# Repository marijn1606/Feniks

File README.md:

# Feniks

Relatively cheap wifi enabled 4 channel BBQ thermometer based on a ESP32-C3.

The system is powered by an 18650 li-ion battery, and has integrated battery charge and protection circuitry.

The temperature probe data is displayed on a small I2C OLED screen as well as a webserver hosted on the ESP.

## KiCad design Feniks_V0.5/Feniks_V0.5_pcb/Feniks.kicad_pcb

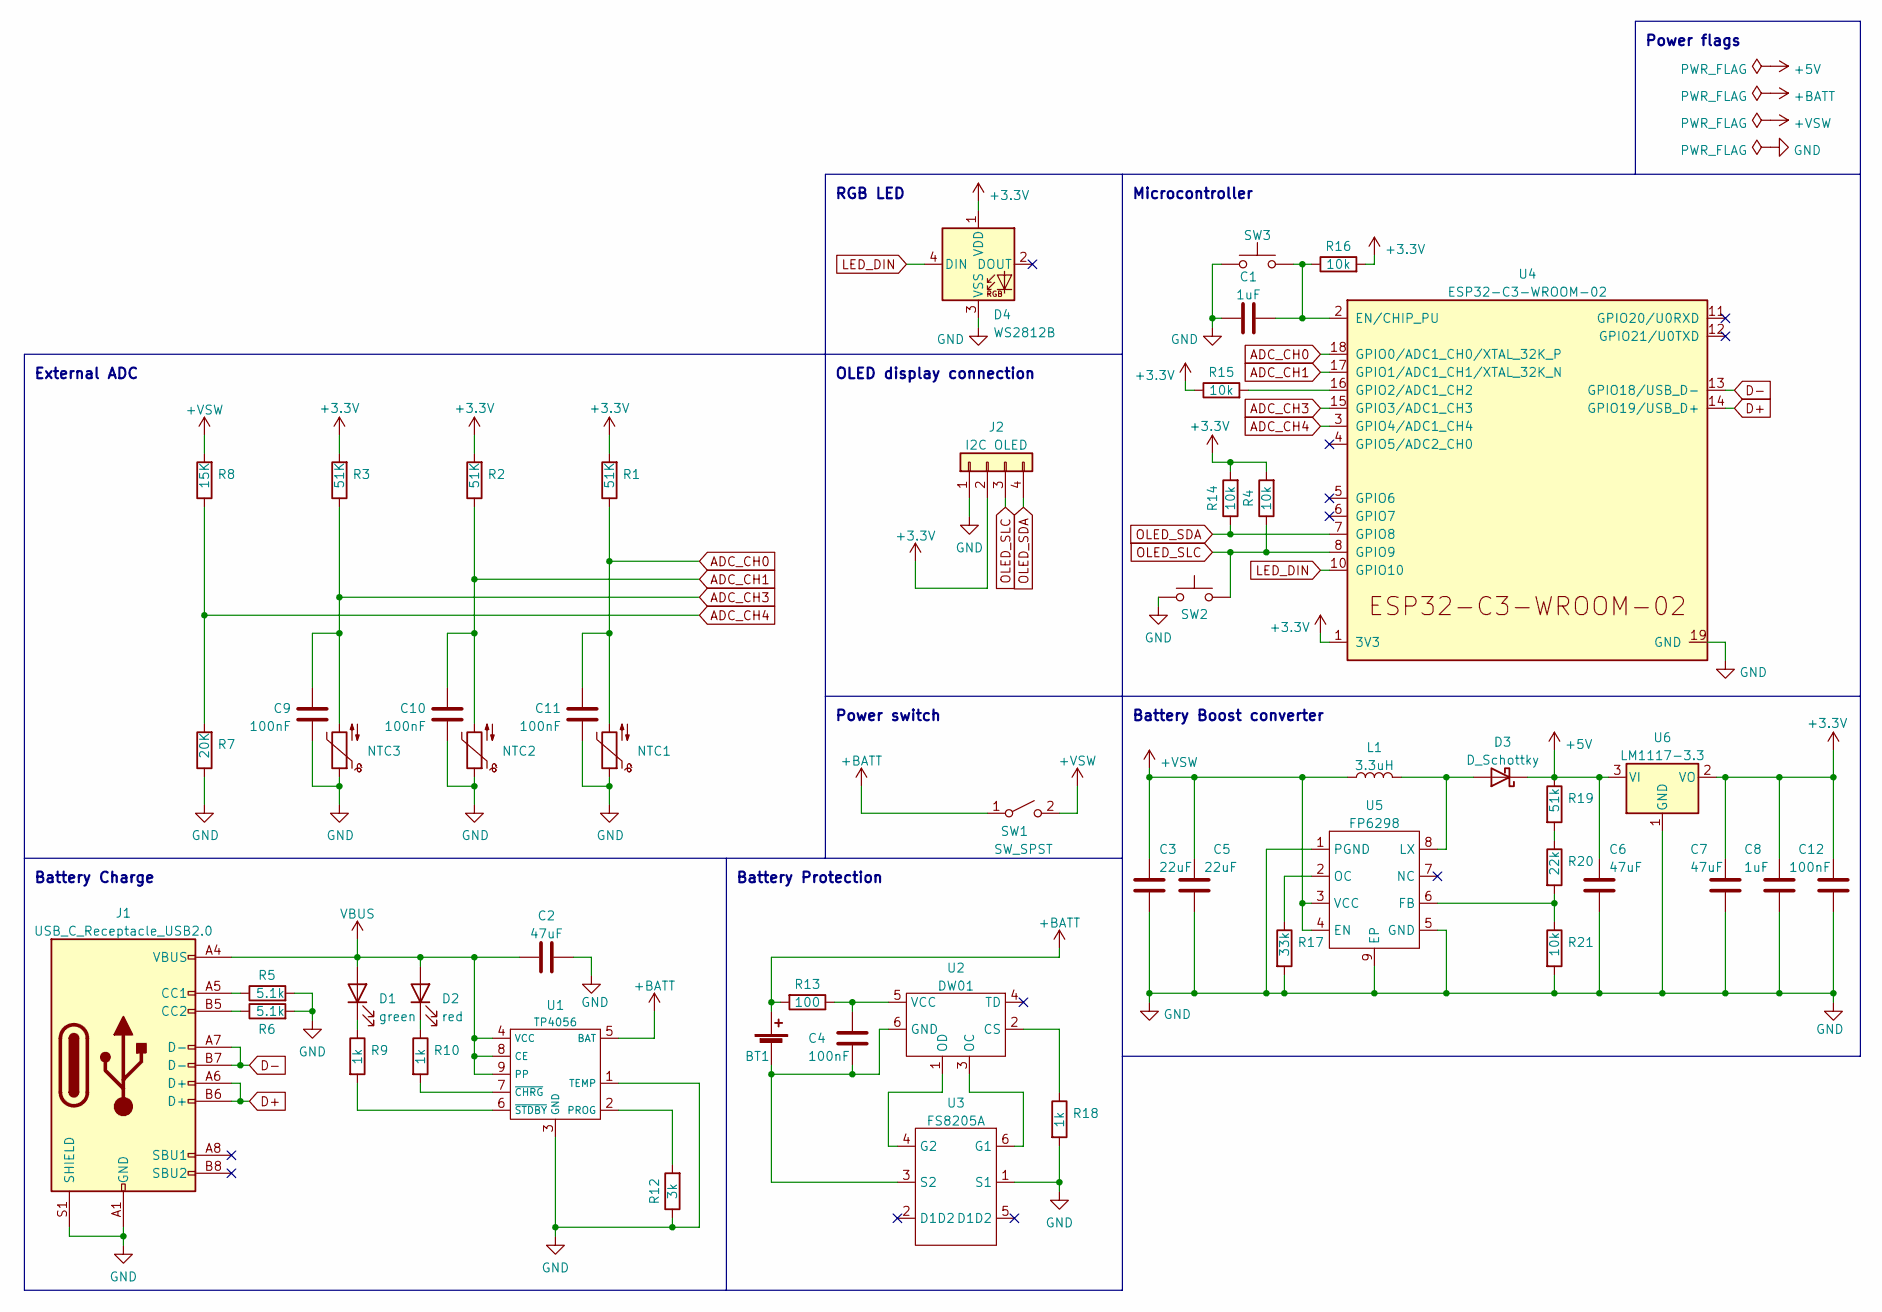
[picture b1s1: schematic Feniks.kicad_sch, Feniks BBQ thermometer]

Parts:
BT1: Battery_Cell; 18650SMT holder
C1, C8: 1uF; C_0805_2012Metric_Pad1.18x1.45mm_HandSolder
C2, C6, C7: 47uF; C_0805_2012Metric_Pad1.18x1.45mm_HandSolder
C3, C5: 22uF; C_0805_2012Metric_Pad1.18x1.45mm_HandSolder
C4, C9, C10, C11, C12: 100nF; C_0805_2012Metric_Pad1.18x1.45mm_HandSolder
D1: green; LED_0805_2012Metric_Pad1.15x1.40mm_HandSolder
D2: red; LED_0805_2012Metric_Pad1.15x1.40mm_HandSolder
D3: D_Schottky; D_SMA
D4: WS2812B; LED_WS2812B_PLCC4_5.0x5.0mm_P3.2mm
J1: USB_C_Receptacle_USB2.0; USB_C_Receptacle_HRO_TYPE-C-31-M-12
J2: I2C OLED; PinSocket_1x04_P2.54mm_Vertical
L1: 3.3uH; CD43
NTC1, NTC2, NTC3: Thermistor_NTC; PinSocket_1x02_P2.54mm_Vertical
R1, R2, R3: 51K; R_0805_2012Metric_Pad1.20x1.40mm_HandSolder
R4, R14, R15, R16, R21: 10k; R_0805_2012Metric_Pad1.20x1.40mm_HandSolder
R5, R6: 5.1k; R_0805_2012Metric_Pad1.20x1.40mm_HandSolder
R7: 20K; R_0805_2012Metric_Pad1.20x1.40mm_HandSolder
R8: 15K; R_0805_2012Metric_Pad1.20x1.40mm_HandSolder
R9, R10, R18: 1k; R_0805_2012Metric_Pad1.20x1.40mm_HandSolder
R12: 3k; R_0805_2012Metric_Pad1.20x1.40mm_HandSolder
R13: 100; R_0805_2012Metric_Pad1.20x1.40mm_HandSolder
R17: 33k; R_0805_2012Metric_Pad1.20x1.40mm_HandSolder
R19: 51k; R_0805_2012Metric_Pad1.20x1.40mm_HandSolder
R20: 22k; R_0805_2012Metric_Pad1.20x1.40mm_HandSolder
SW1: SW_SPST; PinHeader_1x02_P2.54mm_Vertical
SW2, SW3: SW_Push; SW_SPST_CK_RS282G05A3
U1: TP4056; SOIC-8-1EP_3.9x4.9mm_P1.27mm_EP2.29x3mm_ThermalVias
U2: DW01; SOT-23-6_Handsoldering
U3: FS8205A; SOT-23-6_Handsoldering
U4: ESP32-C3-WROOM-02
U5: FP6298; SOIC-8-1EP_3.9x4.9mm_P1.27mm_EP2.29x3mm_ThermalVias
U6: LM1117-3.3; SOT-223-3_TabPin2

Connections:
+3.3V: C7.1, C8.1, C12.1, D4.1 (VDD), J2.2, R1.2, R2.2, R3.2, R4.2, R14.2, R15.1, R16.2, U4.1 (3V3), U6.2 (VO)
+5V: C6.1, D3.1 (K), R19.1, U6.3 (VI)
+BATT: BT1.1 (+), R13.2, SW1.1 (A), U1.5 (BAT)
+VSW: C3.1, C5.1, L1.1, R8.2, SW1.2 (B), U5.3 (VCC), U5.4 (EN)
ADC_CH0: C11.2, NTC1.2, R1.1, U4.18 (GPIO0/ADC1_CH0/XTAL_32K_P)
ADC_CH1: C10.2, NTC2.2, R2.1, U4.17 (GPIO1/ADC1_CH1/XTAL_32K_N)
ADC_CH3: C9.2, NTC3.2, R3.1, U4.15 (GPIO3/ADC1_CH3)
ADC_CH4: R7.2, R8.1, U4.3 (GPIO4/ADC1_CH4)
D+: J1.A6 (D+), J1.B6 (D+), U4.14 (GPIO19/USB_D+)
D-: J1.A7 (D-), J1.B7 (D-), U4.13 (GPIO18/USB_D-)
GND: C1.1, C2.2, C3.2, C5.2, C6.2, C7.2, C8.2, C9.1, C10.1, C11.1, C12.2, D4.3 (VSS), J1.A1 (GND), J1.A12 (GND), J1.B1 (GND), J1.B12 (GND), J1.S1 (SHIELD), J2.1, NTC1.1, NTC2.1, NTC3.1, R5.2, R6.2, R7.1, R12.1, R17.2, R18.2, R21.2, SW2.1, SW3.1, U1.1 (TEMP), U1.3 (GND), U3.1 (S1), U4.9 (GND), U4.19 (GND), U5.1 (PGND), U5.5 (GND), U5.9 (EP), U6.1 (GND)
LED_DIN: D4.4 (DIN), U4.10 (GPIO10)
unnamed: BT1.2 (-), C4.1, U2.6 (GND), U3.3 (S2)
unnamed: C1.2, R16.1, SW3.2, U4.2 (EN/CHIP_PU)
unnamed: C4.2, R13.1, U2.5 (VCC)
unnamed: D1.1 (K), R9.1
unnamed: D2.1 (K), R10.1
unnamed: D3.2 (A), L1.2, U5.8 (LX)
unnamed: J1.A5 (CC1), R5.1
unnamed: J1.B5 (CC2), R6.1
unnamed: R9.2, U1.6 (~STDBY)
unnamed: R10.2, U1.7 (~CHRG)
unnamed: R12.2, U1.2 (PROG)
unnamed: R15.2, U4.16 (GPIO2/ADC1_CH2)
unnamed: R17.1, U5.2 (OC)
unnamed: R18.1, U2.2 (CS)
unnamed: R19.2, R20.1
unnamed: R20.2, R21.1, U5.6 (FB)
unnamed: U2.1 (OD), U3.4 (G2)
unnamed: U2.3 (OC), U3.6 (G1)
OLED_SDA: J2.4, R14.1, U4.7 (GPIO8)
OLED_SLC: J2.3, R4.1, SW2.2, U4.8 (GPIO9)
VBUS: C2.1, D1.2 (A), D2.2 (A), J1.A4 (VBUS), J1.A9 (VBUS), J1.B4 (VBUS), J1.B9 (VBUS), U1.4 (VCC), U1.8 (CE), U1.9 (PP)

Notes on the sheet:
Microcontroller
Power flags
Battery Protection
Battery Boost converter
OLED display connection
RGB LED
Battery Charge
External ADC
Power switch

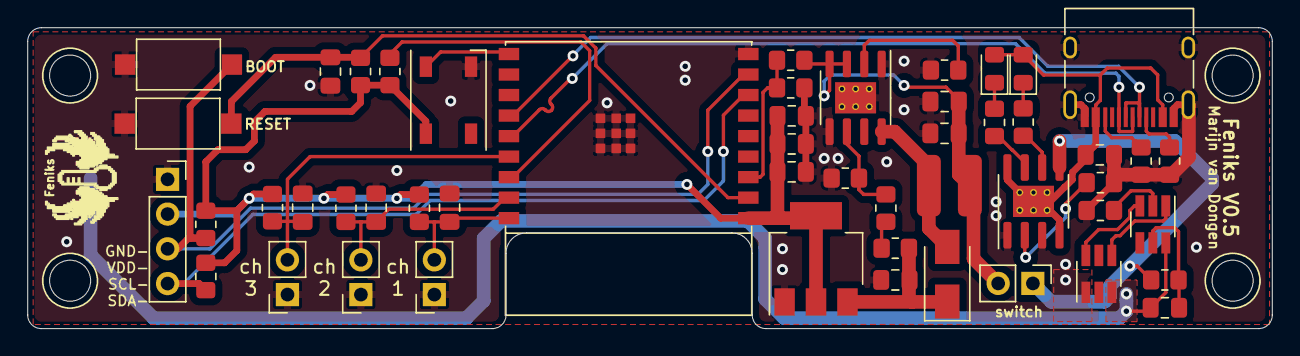
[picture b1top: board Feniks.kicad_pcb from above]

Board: 2 copper layers, 91.0 x 22.0 mm, 52 parts (1 on the bottom side), 33 nets.

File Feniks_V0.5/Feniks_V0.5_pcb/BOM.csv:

"Id;""Designator"";""Package"";""Quantity"";""Designation"";""Supplier and ref"";",,,,,
"1;""C3",C5,C7,C6,C2,"C8"";""C_0805_2012Metric_Pad1.18x1.45mm_HandSolder"";6;""47uF"";;;"
"2;""R10",R18,"R9"";""R_0805_2012Metric_Pad1.20x1.40mm_HandSolder"";3;""1k"";;;",,,
"3;""C11",C12,C4,C10,"C9"";""C_0805_2012Metric_Pad1.18x1.45mm_HandSolder"";5;""100nF"";;;",
"4;""D3"";""D_SMA"";1;""D_Schottky"";;;",,,,,
"5;""R20"";""R_0805_2012Metric_Pad1.20x1.40mm_HandSolder"";1;""68k"";;;",,,,,
"6;""U2"";""SOT-23-6_Handsoldering"";1;""DW01"";;;",,,,,
"7;""U5"";""SOIC-8-1EP_3.9x4.9mm_P1.27mm_EP2.29x3mm_ThermalVias"";1;""FP6298"";;;",,,,,
"8;""D2"";""LED_0805_2012Metric_Pad1.15x1.40mm_HandSolder"";1;""red"";;;",,,,,
"9;""J2"";""PinSocket_1x04_P2.54mm_Vertical"";1;""I2C OLED"";;;",,,,,
"10;""R1",R3,"R2"";""R_0805_2012Metric_Pad1.20x1.40mm_HandSolder"";3;""51K"";;;",,,
"11;""R4",R21,R15,R14,"R16"";""R_0805_2012Metric_Pad1.20x1.40mm_HandSolder"";5;""10k"";;;",
"12;""U4"";""ESP32-C3-WROOM-02"";1;""ESP32-C3-WROOM-02"";;;",,,,,
"13;""L1"";""CD43"";1;""3.3uH"";;;",,,,,
"14;""R5",R6,"R19"";""R_0805_2012Metric_Pad1.20x1.40mm_HandSolder"";3;""5.1k"";;;",,,
"15;""NTC3",NTC2,"NTC1"";""PinSocket_1x02_P2.54mm_Vertical"";3;""Thermistor_NTC"";;;",,,
"16;""C1"";""C_0805_2012Metric_Pad1.18x1.45mm_HandSolder"";1;""1uF"";;;",,,,,
"17;""SW3","SW2"";""SW_SPST_CK_RS282G05A3"";2;""SW_Push"";;;",,,,
"18;""U1"";""SOIC-8-1EP_3.9x4.9mm_P1.27mm_EP2.29x3mm_ThermalVias"";1;""TP4056"";;;",,,,,
"19;""U3"";""SOT-23-6_Handsoldering"";1;""FS8205A"";;;",,,,,
"20;""R8"";""R_0805_2012Metric_Pad1.20x1.40mm_HandSolder"";1;""15K"";;;",,,,,
"21;""U6"";""SOT-223-3_TabPin2"";1;""LM1117-3.3"";;;",,,,,
"22;""SW1"";""PinHeader_1x02_P2.54mm_Vertical"";1;""SW_SPST"";;;",,,,,
"23;""J1"";""USB_C_Receptacle_HRO_TYPE-C-31-M-12"";1;""USB_C_Receptacle_USB2.0"";;;",,,,,
"24;""D4"";""LED_WS2812B_PLCC4_5.0x5.0mm_P3.2mm"";1;""WS2812B"";;;",,,,,
"25;""R17"";""R_0805_2012Metric_Pad1.20x1.40mm_HandSolder"";1;""26k"";;;",,,,,
"26;""R7"";""R_0805_2012Metric_Pad1.20x1.40mm_HandSolder"";1;""20K"";;;",,,,,
"27;""R12"";""R_0805_2012Metric_Pad1.20x1.40mm_HandSolder"";1;""3k"";;;",,,,,
"28;""D1"";""LED_0805_2012Metric_Pad1.15x1.40mm_HandSolder"";1;""green"";;;",,,,,
"29;""R13"";""R_0805_2012Metric_Pad1.20x1.40mm_HandSolder"";1;""100"";;;",,,,,

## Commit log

2023-01-11 Fresh start
2023-10-13 clean up
